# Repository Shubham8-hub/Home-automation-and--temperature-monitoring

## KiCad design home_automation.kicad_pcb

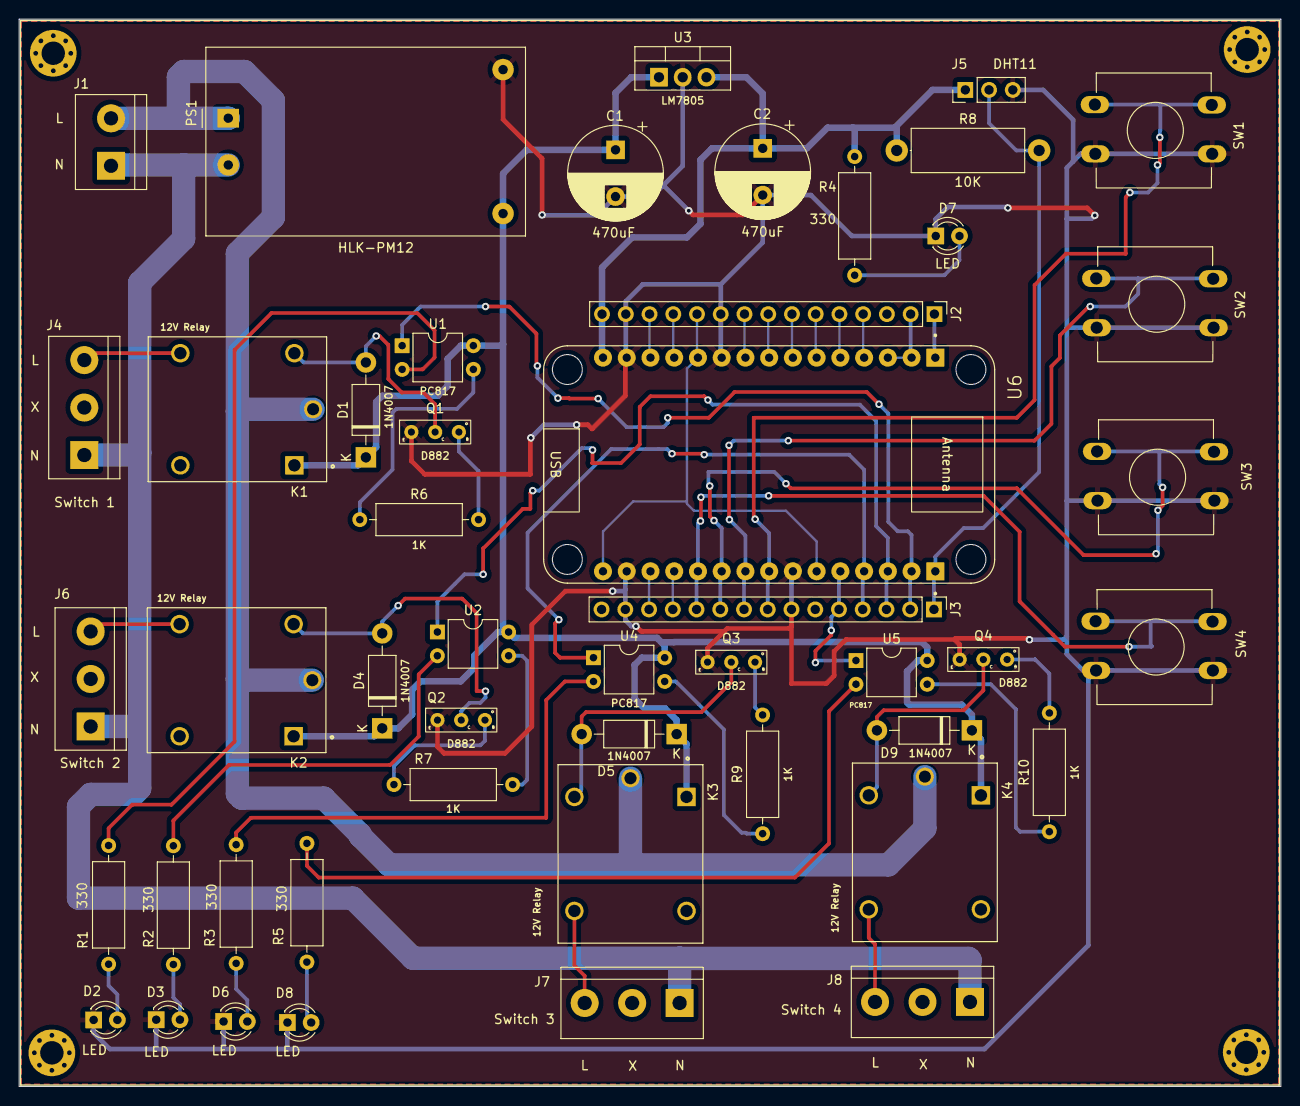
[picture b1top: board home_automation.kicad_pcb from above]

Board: 2 copper layers, 135.0 x 114.2 mm, 48 parts (0 on the bottom side), 52 nets.

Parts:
C1, C2: 470uF; CP_Radial_D10.0mm_P5.00mm
D1, D4, D5, D9: 1N4007; D_DO-41_SOD81_P10.16mm_Horizontal
D2, D3, D6, D7, D8: LED; LED_D3.0mm
J1: AC_in; TerminalBlock_bornier-2_P5.08mm
J2, J3: NodeMCU Header; PinHeader_1x15_P2.54mm_Vertical
J4: Sw_1; TerminalBlock_bornier-3_P5.08mm
J5: DHT11; PinHeader_1x03_P2.54mm_Vertical
J6: Sw_2; TerminalBlock_bornier-3_P5.08mm
J7: Sw_3; TerminalBlock_bornier-3_P5.08mm
J8: Sw_4; TerminalBlock_bornier-3_P5.08mm
K1, K2, K3, K4: 12V Relay; RELAY_SRD-05VDC-SL-C
PS1: HLK-PM12; Converter_ACDC_HiLink_HLK-PMxx
Q1, Q2, Q3, Q4: D882; D882_NPN_Transistor
R1, R2, R3, R4, R5: 330; R_Axial_DIN0309_L9.0mm_D3.2mm_P12.70mm_Horizontal
R6, R7, R9, R10: 1K; R_Axial_DIN0309_L9.0mm_D3.2mm_P12.70mm_Horizontal
R8: 10K; R_Axial_DIN0414_L11.9mm_D4.5mm_P15.24mm_Horizontal
SW1, SW2, SW3, SW4: SW_DIP_x02; 4_pin_Button
U1, U2, U4, U5: PC817; DIP-4_W7.62mm
U3: LM7805; TO-220-3_Vertical
U6: NodeMCU; nodemcu_esp8266

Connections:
/3V3-1: J2.11, U6.3V3
/5v: C2.1, J2.15, J5.1, R4.1, R8.1, U3.3 (VO), U6.Vin
/12v: C1.1, D1.1 (K), D4.1 (K), D5.1 (K), D9.1 (K), K1.A1 (Coil), K2.A1 (Coil), K3.A1 (Coil), K4.A1 (Coil), PS1.4 (+Vout), U1.4, U2.4, U3.1 (VI), U4.4, U5.4
/A0: J2.1, U6.A0
/Base: Q1.1 (B), R6.2
/Base_2: Q2.1 (B), R7.2
/Base_3: Q3.1 (B), R9.2
/Base_4: Q4.1 (B), R10.2
/CLK: J2.9, U6.CLK
/CMD: J2.7, U6.CMD
/Collector: D1.2 (A), K1.A2 (Coil), Q1.2 (C)
/Collector_2: D4.2 (A), K2.A2 (Coil), Q2.2 (C)
/Collector_3: D5.2 (A), K3.A2 (Coil), Q3.2 (C)
/Collector_4: D9.2 (A), K4.A2 (Coil), Q4.2 (C)
/D0: J3.1, J5.2, R8.2, U6.D0
/D1: J3.2, U1.1, U6.D1
/D2: J3.3, U2.1, U6.D2
/D3: J3.4, U4.1, U6.D3
/D4: J3.5, U5.1, U6.D4
/D5: J3.8, SW1.1, SW1.2, U6.D5
/D6: J3.9, SW2.1, SW2.2, U6.D6
/D7: J3.10, SW3.1, SW3.2, U6.D7
/D8: J3.11, SW4.1, SW4.2, U6.D8
/EN: J2.12, U6.EN
/L: J1.2, K1.COM, K2.COM, K3.COM, K4.COM, PS1.1 (AC/L)
/LED: D7.2 (A), R4.2
/LED_1: D2.2 (A), R1.2
/LED_2: D3.2 (A), R2.2
/LED_3: D6.2 (A), R3.2
/LED_4: D8.2 (A), R5.2
/N: J1.1, J4.1, J6.1, J7.1, J8.1, PS1.2 (AC/N)
/NO: J4.3, K1.NO
/NO_2: J6.3, K2.NO
/NO_3: J7.3, K3.NO
/NO_4: J8.3, K4.NO
/RST: J2.13, U6.RST
/RSV1: J2.2, U6.RSV
/RX: J3.12, U6.RX
/SD0: J2.8, U6.SD0
/SD1: J2.6, U6.SD1
/SD2: J2.5, U6.SD2
/SD3: J2.4, U6.SD3
/TX: J3.13, U6.TX
GND: C1.2, C2.2, D2.1 (K), D3.1 (K), D6.1 (K), D7.1 (K), D8.1 (K), J2.10, J2.14, J3.7, J3.14, J5.3, PS1.3 (-Vout), Q1.3 (E), Q2.3 (E), Q3.3 (E), Q4.3 (E), SW1.3, SW1.4, SW2.3, SW2.4, SW3.3, SW3.4, SW4.3, SW4.4, U3.2 (GND), U6.GND
unnamed: R1.1, U1.2
unnamed: R2.1, U2.2
unnamed: R3.1, U4.2
unnamed: R5.1, U5.2
unnamed: R6.1, U1.3
unnamed: R7.1, U2.3
unnamed: R9.1, U4.3
unnamed: R10.1, U5.3

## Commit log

2022-10-26 Home automation pcb started
2022-10-26 Components gathered
2022-10-26 Anotate the Components
2022-10-26 Power section Wiring Completed
2022-10-26 12v to 5v Wiring Completed
2022-10-26 DHT11 to NodeMCU Wiring Completed
2022-10-27 Relay wiring completed
2022-10-27 Correction done in schematic diagram
2022-10-27 modification in .gitignore file
2022-10-27 Updated components from Schematic to PCB
2022-10-28 Changes in PCB
2022-10-28 Placing and Back layer wiring
2022-10-28 Replaced connectors
2022-10-28 Routing Completed
2022-11-27 code for home automation
